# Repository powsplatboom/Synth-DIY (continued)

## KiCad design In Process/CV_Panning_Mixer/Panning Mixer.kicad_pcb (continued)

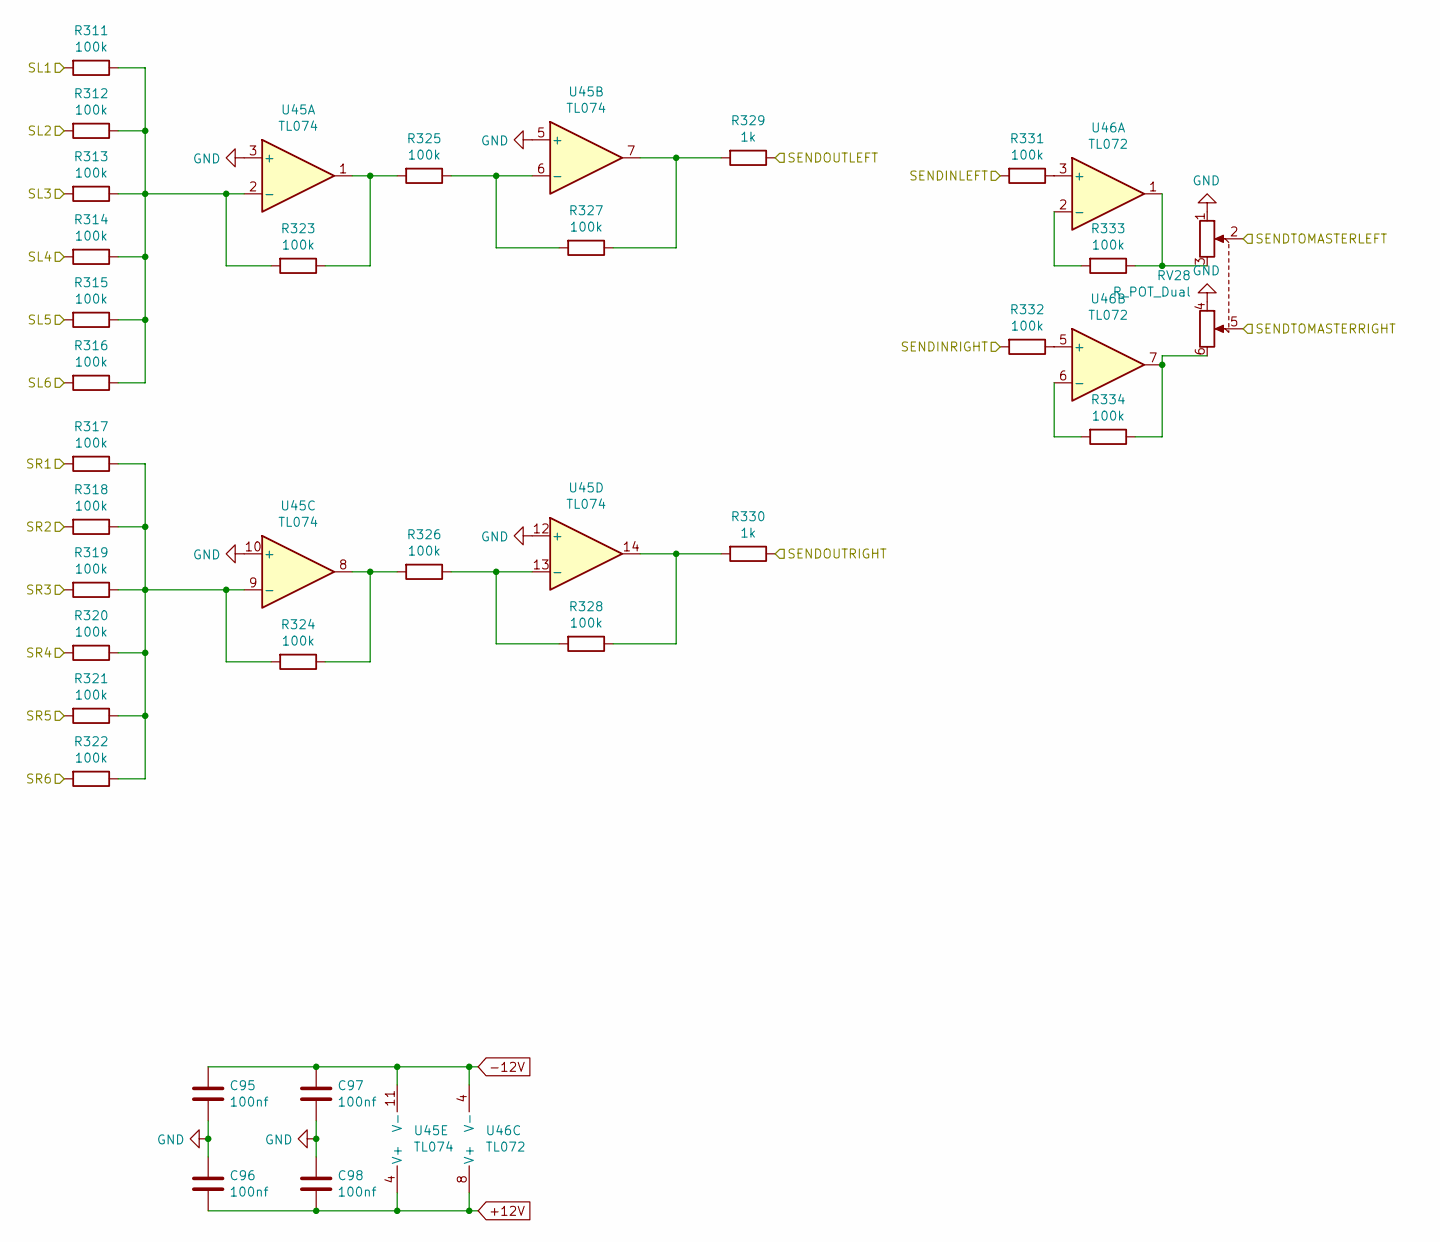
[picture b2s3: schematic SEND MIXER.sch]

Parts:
C91, C92, C93, C94: 100nf; C_0603_1608Metric
R287, R288, R289, R290, R291, R292, R293, R294, R295, R296, R297, R298, R299, R300, R301, R302, R303, R304, R307, R308, R309, R310: 100k; R_0603_1608Metric
R305, R306: 1k; R_0603_1608Metric
RV27: R_POT_Dual; Potentiometer_Alpha_RD902F-40-00D_Dual_Vertical
U43: TL074; SOIC-14_3.9x8.7mm_P1.27mm
U44: TL072; SOIC-8_3.9x4.9mm_P1.27mm

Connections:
+12V: C92.2, C94.2, U43.4 (V+), U44.8 (V+); also elsewhere on the board
-12V: C91.1, C93.1, U43.11 (V-), U44.4 (V-); also elsewhere on the board
GND: C91.2, C92.1, C93.2, C94.1, RV27.1, RV27.4, U43.3 (+), U43.5 (+), U43.10 (+), U43.12 (+); also elsewhere on the board
unnamed: R287.1, R288.1, R289.1, R290.1, R291.1, R292.1, R299.2, U43.2 (-)
unnamed: R293.1, R294.1, R295.1, R296.1, R297.1, R298.1, R300.2, U43.9 (-)
unnamed: R299.1, R301.2, U43.1
unnamed: R300.1, R302.2, U43.8
unnamed: R301.1, R303.2, U43.6 (-)
unnamed: R302.1, R304.2, U43.13 (-)
unnamed: R303.1, R305.2, U43.7
unnamed: R304.1, R306.2, U43.14
unnamed: R307.1, U44.3 (+)
unnamed: R308.1, U44.5 (+)
unnamed: R309.1, RV27.3, U44.1
unnamed: R309.2, U44.2 (-)
unnamed: R310.1, RV27.6, U44.7
unnamed: R310.2, U44.6 (-)
SENDINRIGHT_1: R308.2; also elsewhere on the board
SENDOUTLEFT_1: R305.1; also elsewhere on the board
SENDOUTRIGHT_1: R306.1; also elsewhere on the board
SENDTOMASTERLEFT_1: RV27.2; also elsewhere on the board
SENDTOMASTERRIGHT_1: RV27.5; also elsewhere on the board
SL1_1: R287.2; also elsewhere on the board
SL2_1: R288.2; also elsewhere on the board
SL3_1: R289.2; also elsewhere on the board
SL4_1: R290.2; also elsewhere on the board
SL5_1: R291.2; also elsewhere on the board
SL6_1: R292.2; also elsewhere on the board
SR1_1: R293.2; also elsewhere on the board
SR2_1: R294.2; also elsewhere on the board
SR3_1: R295.2; also elsewhere on the board
SR4_1: R296.2; also elsewhere on the board
SR5_1: R297.2; also elsewhere on the board
SR6_1: R298.2; also elsewhere on the board

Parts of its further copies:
C95, C96, C97, C98: 100nf; C_0603_1608Metric
R311, R312, R313, R314, R315, R316, R317, R318, R319, R320, R321, R322, R323, R324, R325, R326, R327, R328, R331, R332, R333, R334: 100k; R_0603_1608Metric
R329, R330: 1k; R_0603_1608Metric
RV28: R_POT_Dual; Potentiometer_Alpha_RD902F-40-00D_Dual_Vertical
U45: TL074; SOIC-14_3.9x8.7mm_P1.27mm
U46: TL072; SOIC-8_3.9x4.9mm_P1.27mm

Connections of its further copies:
+12V: C96.2, C98.2, U45.4 (V+), U46.8 (V+); also elsewhere on the board
-12V: C95.1, C97.1, U45.11 (V-), U46.4 (V-); also elsewhere on the board
GND: C95.2, C96.1, C97.2, C98.1, RV28.1, RV28.4, U45.3 (+), U45.5 (+), U45.10 (+), U45.12 (+); also elsewhere on the board
unnamed: R311.1, R312.1, R313.1, R314.1, R315.1, R316.1, R323.2, U45.2 (-)
unnamed: R317.1, R318.1, R319.1, R320.1, R321.1, R322.1, R324.2, U45.9 (-)
unnamed: R323.1, R325.2, U45.1
unnamed: R324.1, R326.2, U45.8
unnamed: R325.1, R327.2, U45.6 (-)
unnamed: R326.1, R328.2, U45.13 (-)
unnamed: R327.1, R329.2, U45.7
unnamed: R328.1, R330.2, U45.14
unnamed: R331.1, U46.3 (+)
unnamed: R332.1, U46.5 (+)
unnamed: R333.1, RV28.3, U46.1
unnamed: R333.2, U46.2 (-)
unnamed: R334.1, RV28.6, U46.7
unnamed: R334.2, U46.6 (-)
SENDINRIGHT_2: R332.2; also elsewhere on the board
SENDOUTLEFT_2: R329.1; also elsewhere on the board
SENDOUTRIGHT_2: R330.1; also elsewhere on the board
SENDTOMASTERLEFT_2: RV28.2; also elsewhere on the board
SENDTOMASTERRIGHT_2: RV28.5; also elsewhere on the board
SL1_2: R311.2; also elsewhere on the board
SL2_2: R312.2; also elsewhere on the board
SL3_2: R313.2; also elsewhere on the board
SL4_2: R314.2; also elsewhere on the board
SL5_2: R315.2; also elsewhere on the board
SL6_2: R316.2; also elsewhere on the board
SR1_2: R317.2; also elsewhere on the board
SR2_2: R318.2; also elsewhere on the board
SR3_2: R319.2; also elsewhere on the board
SR4_2: R320.2; also elsewhere on the board
SR5_2: R321.2; also elsewhere on the board
SR6_2: R322.2; also elsewhere on the board

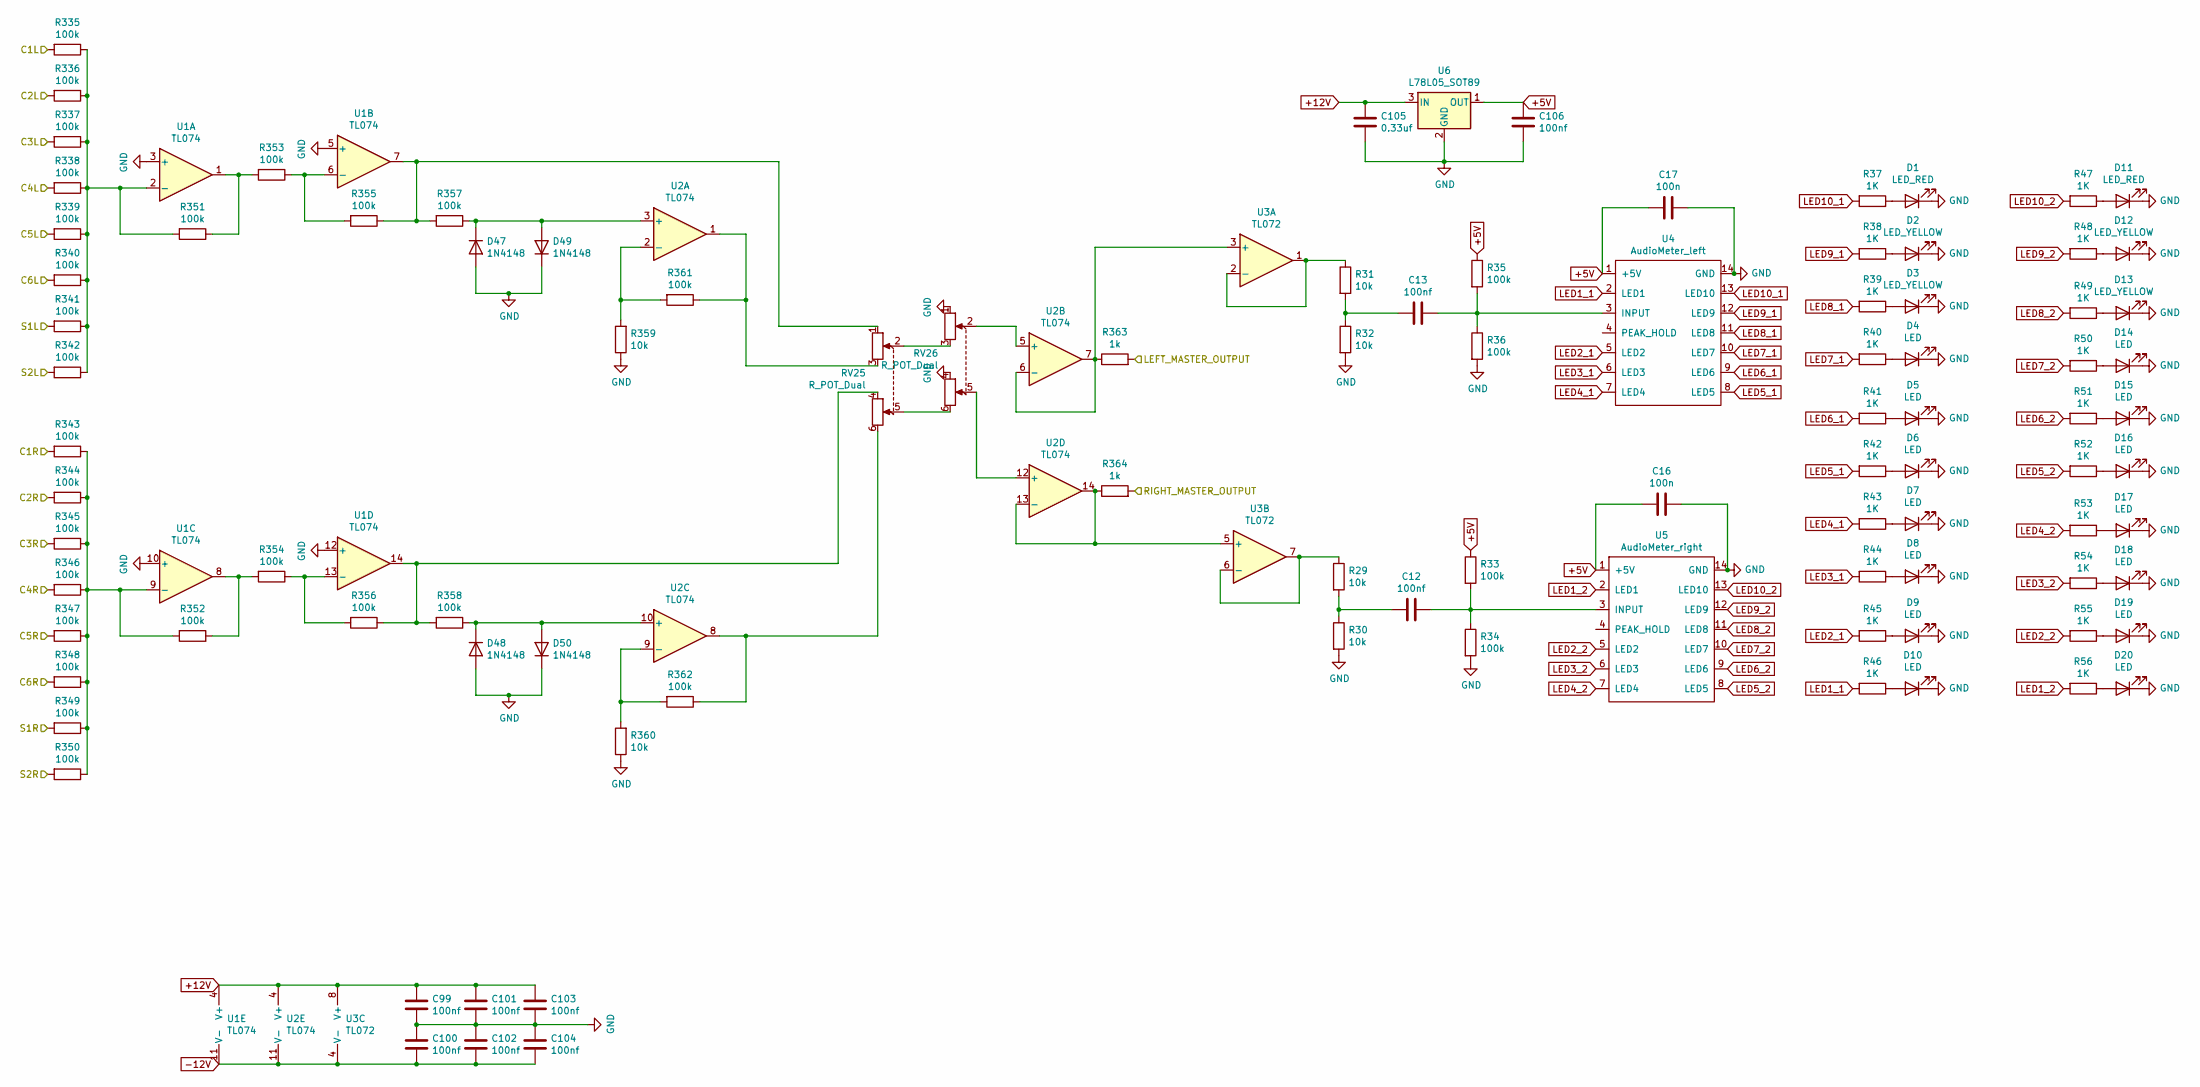
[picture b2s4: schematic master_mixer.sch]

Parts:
C12, C13, C99, C100, C101, C102, C103, C104, C106: 100nf; C_0603_1608Metric
C16, C17: 100n; C_0603_1608Metric
C105: 0.33uf; C_0603_1608Metric
D1, D11: LED_RED; LED_0805_2012Metric
D2, D3, D12, D13: LED_YELLOW; LED_0805_2012Metric
D4, D5, D6, D7, D8, D9, D10, D14, D15, D16, D17, D18, D19, D20: LED; LED_0805_2012Metric
D47, D48, D49, D50: 1N4148; D_DO-35_SOD27_P7.62mm_Horizontal
R29, R30, R31, R32, R359, R360: 10k; R_0603_1608Metric
R33, R34, R35, R36, R335, R336, R337, R338, R339, R340, R341, R342, R343, R344, R345, R346, R347, R348, R349, R350, R351, R352, R353, R354, R355, R356, R357, R358, R361, R362: 100k; R_0603_1608Metric
R37, R38, R39, R40, R41, R42, R43, R44, R45, R46, R47, R48, R49, R50, R51, R52, R53, R54, R55, R56: 1K; R_0603_1608Metric
R363, R364: 1k; R_0603_1608Metric
RV25, RV26: R_POT_Dual; Potentiometer_Alpha_RD902F-40-00D_Dual_Vertical
U1, U2: TL074; SOIC-14_3.9x8.7mm_P1.27mm
U3: TL072; SOIC-8_3.9x4.9mm_P1.27mm
U4: AudioMeter_left; DIP-14_W7.62mm_Socket_LongPads
U5: AudioMeter_right; DIP-14_W7.62mm_Socket_LongPads
U6: L78L05_SOT89; SOT-89-3

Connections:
+5V: C16.1, C17.1, C106.1, R33.1, R35.1, U4.1 (+5V), U5.1 (+5V), U6.1 (OUT)
+12V: C99.1, C101.1, C103.1, C105.1, U1.4 (V+), U2.4 (V+), U3.8 (V+), U6.3 (IN); also elsewhere on the board
-12V: C100.2, C102.2, C104.2, U1.11 (V-), U2.11 (V-), U3.4 (V-); also elsewhere on the board
GND: C16.2, C17.2, C99.2, C100.1, C101.2, C102.1, C103.2, C104.1, C105.2, C106.2, D1.1 (K), D2.1 (K), D3.1 (K), D4.1 (K), D5.1 (K), D6.1 (K), D7.1 (K), D8.1 (K), D9.1 (K), D10.1 (K), D11.1 (K), D12.1 (K), D13.1 (K), D14.1 (K), D15.1 (K), D16.1 (K), D17.1 (K), D18.1 (K), D19.1 (K), D20.1 (K), D47.2 (A), D48.2 (A), D49.1 (K), D50.1 (K), R30.2, R32.2, R34.2, R36.2, R359.1, R360.1, RV26.1, RV26.4, U1.3 (+), U1.5 (+), U1.10 (+), U1.12 (+), U4.14 (GND), U5.14 (GND), U6.2 (GND); also elsewhere on the board
LED1_1: R46.2, U4.2 (LED1)
LED1_2: R56.2, U5.2 (LED1)
LED2_1: R45.2, U4.5 (LED2)
LED2_2: R55.2, U5.5 (LED2)
LED3_1: R44.2, U4.6 (LED3)
LED3_2: R54.2, U5.6 (LED3)
LED4_1: R43.2, U4.7 (LED4)
LED4_2: R53.2, U5.7 (LED4)
LED5_1: R42.2, U4.8 (LED5)
LED5_2: R52.2, U5.8 (LED5)
LED6_1: R41.2, U4.9 (LED6)
LED6_2: R51.2, U5.9 (LED6)
LED7_1: R40.2, U4.10 (LED7)
LED7_2: R50.2, U5.10 (LED7)
LED8_1: R39.2, U4.11 (LED8)
LED8_2: R49.2, U5.11 (LED8)
LED9_1: R38.2, U4.12 (LED9)
LED9_2: R48.2, U5.12 (LED9)
LED10_1: R37.2, U4.13 (LED10)
LED10_2: R47.2, U5.13 (LED10)
LEFT_MASTER_OUTPUT: R363.2; also elsewhere on the board
unnamed: C12.1, R33.2, R34.1, U5.3 (INPUT)
unnamed: C12.2, R29.2, R30.1
unnamed: C13.1, R35.2, R36.1, U4.3 (INPUT)
unnamed: C13.2, R31.2, R32.1
unnamed: D1.2 (A), R37.1
unnamed: D2.2 (A), R38.1
unnamed: D3.2 (A), R39.1
unnamed: D4.2 (A), R40.1
unnamed: D5.2 (A), R41.1
unnamed: D6.2 (A), R42.1
unnamed: D7.2 (A), R43.1
unnamed: D8.2 (A), R44.1
unnamed: D9.2 (A), R45.1
unnamed: D10.2 (A), R46.1
unnamed: D11.2 (A), R47.1
unnamed: D12.2 (A), R48.1
unnamed: D13.2 (A), R49.1
unnamed: D14.2 (A), R50.1
unnamed: D15.2 (A), R51.1
unnamed: D16.2 (A), R52.1
unnamed: D17.2 (A), R53.1
unnamed: D18.2 (A), R54.1
unnamed: D19.2 (A), R55.1
unnamed: D20.2 (A), R56.1
unnamed: D47.1 (K), D49.2 (A), R357.1, U2.3 (+)
unnamed: D48.1 (K), D50.2 (A), R358.1, U2.10 (+)
unnamed: R29.1, U3.6 (-), U3.7
unnamed: R31.1, U3.1, U3.2 (-)
unnamed: R335.1, R336.1, R337.1, R338.1, R339.1, R340.1, R341.1, R342.1, R351.2, U1.2 (-)
unnamed: R343.1, R344.1, R345.1, R346.1, R347.1, R348.1, R349.1, R350.1, R352.2, U1.9 (-)
unnamed: R351.1, R353.2, U1.1
unnamed: R352.1, R354.2, U1.8
unnamed: R353.1, R355.2, U1.6 (-)
unnamed: R354.1, R356.2, U1.13 (-)
unnamed: R355.1, R357.2, RV25.1, U1.7
unnamed: R356.1, R358.2, RV25.4, U1.14
unnamed: R359.2, R361.2, U2.2 (-)
unnamed: R360.2, R362.2, U2.9 (-)
unnamed: R361.1, RV25.3, U2.1
unnamed: R362.1, RV25.6, U2.8
unnamed: R363.1, U2.6 (-), U2.7, U3.3 (+)
unnamed: R364.1, U2.13 (-), U2.14, U3.5 (+)
unnamed: RV25.2, RV26.3
unnamed: RV25.5, RV26.6
unnamed: RV26.2, U2.5 (+)
unnamed: RV26.5, U2.12 (+)
OUT_LEFT1: R335.2; also elsewhere on the board
OUT_LEFT2: R336.2; also elsewhere on the board
OUT_LEFT3: R337.2; also elsewhere on the board
OUT_LEFT4: R338.2; also elsewhere on the board
OUT_LEFT5: R339.2; also elsewhere on the board
OUT_LEFT6: R340.2; also elsewhere on the board
OUT_RIGHT1: R343.2; also elsewhere on the board
OUT_RIGHT2: R344.2; also elsewhere on the board
OUT_RIGHT3: R345.2; also elsewhere on the board
OUT_RIGHT4: R346.2; also elsewhere on the board
OUT_RIGHT5: R347.2; also elsewhere on the board
OUT_RIGHT6: R348.2; also elsewhere on the board
RIGHT_MASTER_OUTPUT: R364.2; also elsewhere on the board
SENDTOMASTERLEFT_1: R341.2; also elsewhere on the board
SENDTOMASTERLEFT_2: R342.2; also elsewhere on the board
SENDTOMASTERRIGHT_1: R349.2; also elsewhere on the board
SENDTOMASTERRIGHT_2: R350.2; also elsewhere on the board

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
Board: 4 copper layers, 633 parts (122 on the bottom side), 482 nets, no tracks yet.

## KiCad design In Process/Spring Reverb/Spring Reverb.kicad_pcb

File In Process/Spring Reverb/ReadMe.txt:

Board has been spun, but not populated. Will respin before testing, as some component circuit blocks have been discovered to have issues.

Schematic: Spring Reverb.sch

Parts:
C1, C2, C6, C10, C28, C39, C41, C42, C53: 10u; CP_Elec_4x5.3
C3, C7, C8, C9, C11, C12, C13, C14, C15, C16, C17, C18, C19, C20, C21, C22, C23, C24, C26, C27, C29, C30, C33, C34, C35, C36, C44, C45, C64: 100n; C_0603_1608Metric
C4: 0.33u; C_0603_1608Metric
C5, C65, C66, C67: 10uf; CP_Elec_4x5.3
C25: 22n; C_0603_1608Metric
C31, C38, C50, C51, C58, C59: 1nf; C_0603_1608Metric
C32: 470p; C_0603_1608Metric
C37, C55, C56: 4.7nf; C_0603_1608Metric
C40, C60, C61: 0.47nf; C_0603_1608Metric
C43: 100p; C_0603_1608Metric
C46: 22u; CP_Elec_4x5.3
C49, C62: 22p; C_0603_1608Metric
C63: 100nf; C_0603_1608Metric
D1, D2: B5819W; D_SOD-123
D3, D4, D11, D13: 1N4148; D_SOD-123
D5, D6, D7, D8, D9, D10, D12, D16, D17, D18, D19, D20, D21, D22, D23, D24, D25: LED; LED_1206_3216Metric_Pad1.42x1.75mm_HandSolder
D14: LED_RED; LED_1206_3216Metric_Pad1.42x1.75mm_HandSolder
D15: LED_YELLOW; LED_1206_3216Metric_Pad1.42x1.75mm_HandSolder
IC1: THAT4305Q16-U; QSOP-16_3.9x4.9mm_P0.635mm; Manufacturer_Part_Number THAT4305Q16-U
J1: Conn_02x05_Odd_Even; PinHeader_2x05_P2.54mm_Vertical
J2, J3, J4, J5, J6, J7, J8, J9, J10, J11, J13, J14, J18, J19: PJ301_THONKICONN; PJ-3001_Mono_Phone
Q1: BC849; SOT-23
Q2: BC859; SOT-23
Q3, Q4, Q11, Q12, Q13, Q14, Q15: BC848; SOT-23
Q5, Q6, Q7, Q8, Q9, Q10: BC858; SOT-23
R1, R2, R3, R7, R8, R9, R10, R13, R15, R24, R32, R36, R37, R60, R61, R62, R63, R91, R98, R99, R100, R101, R102, R103, R121, R122, R127, R128, R129, R130, R132, R133, R144, R145, R146, R147, R148, R149, R150, R151, R152: 100k; R_0603_1608Metric
R4, R19, R20, R34, R39, R43, R45, R46, R48, R50, R52, R56, R57, R66, R67, R73, R74, R75, R76, R77, R78, R81, R82, R87, R88, R93, R94, R108, R109, R115, R116, R119, R120, R124, R125, R126: 10k; R_0603_1608Metric
R5: 50k; R_0603_1608Metric
R6: 150; R_0603_1608Metric
R11, R12: 6k8; R_0603_1608Metric
R14, R18, R92: 5k; R_0603_1608Metric
R16, R17: 10; R_0603_1608Metric
R21: 3k3; R_0603_1608Metric
R22, R23, R95: 1k; R_0603_1608Metric
R25, R53, R70, R96, R97, R110, R111, R112, R113: 20k; R_0603_1608Metric
R26: 40k; R_0603_1608Metric
R31: 2k2; R_0603_1608Metric
R33: 220; R_0603_1608Metric
R35, R38, R47, R51, R58, R59, R64, R65, R79, R80, R85, R86: 220R; R_0603_1608Metric
R40, R68, R69: 1.8k; R_0603_1608Metric
R41, R71, R72: 470k; R_0603_1608Metric
R42: 22k; R_0603_1608Metric
R44: 2k; R_0603_1608Metric
R49, R83, R84: 4.7k; R_0603_1608Metric
R54: 33k; R_0603_1608Metric
R55: 6k2; R_0603_1608Metric
R89, R131: 5k1; R_0603_1608Metric
R90: 360k; R_0603_1608Metric
R104, R105: 82k; R_0603_1608Metric
R106, R107, R117, R118: 100R; R_0603_1608Metric
R114: 1k43; R_0603_1608Metric
R123: 487k; R_0603_1608Metric
R134, R135, R136, R137, R138, R139, R140, R141, R142, R143: 1K; R_0603_1608Metric
RV3, RV4, RV5, RV6, RV7, RV8, RV9, RV10, RV11, RV13, RV14: 100k; Potentiometer_Alpha_RD901F-40-00D_Single_Vertical
RV12, RV15, RV16, RV19, RV20: 10k; Potentiometer_Alpha_RD901F-40-00D_Single_Vertical
RV17, RV18: 100k; Potentiometer_Bourns_3266Y_Vertical
RV21, RV22: R_POT_Dual_Separate; Potentiometer_Alpha_RD902F-40-00D_Dual_Vertical
SW1, SW2, SW3, SW4, SW5: SW_DPDT_x2; DPDT_ThroughHole
TP5, TP6: TestPoint A; TestPoint_Bridge_Pitch2.54mm_Drill1.0mm
TP7, TP8: TestPoint C; TestPoint_Bridge_Pitch2.54mm_Drill1.0mm
TP9, TP12: TestPoint D; TestPoint_Bridge_Pitch2.54mm_Drill1.0mm
TP10, TP11: TestPoint B; TestPoint_Bridge_Pitch2.54mm_Drill1.0mm
U1, U3, U4, U6, U7, U9, U11, U12: TL074; SOIC-14_3.9x8.7mm_P1.27mm
U2, U8, U10: LM13700; SO-16_3.9x9.9mm_P1.27mm
U5: NE5532; SOIC-8_3.9x4.9mm_P1.27mm
U13: L78L05_SO8; SOIC-8_3.9x4.9mm_P1.27mm
U15: AudioMeter_left; DIP-14_W7.62mm_Socket_LongPads

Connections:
+5V: C7.1, C64.1, R127.1, U13.1 (OUT), U15.1 (+5V)
+12V: C1.1, C4.1, C8.2, C11.2, C13.2, C15.2, C17.2, C19.2, C21.2, C23.2, C26.2, C29.2, C33.2, C35.2, C44.1, C46.1, D1.1 (K), IC1.9 (VCC), Q1.3 (C), R11.2, R22.2, R23.2, R95.2, R96.2, R97.2, R110.2, R111.2, R112.2, R113.2, RV4.3, RV7.3, RV8.3, RV12.1, RV16.1, RV17.1, RV18.1, U1.4 (V+), U2.11 (V+), U3.4 (V+), U4.4 (V+), U5.8 (V+), U6.4 (V+), U7.4 (V+), U8.11 (V+), U9.4 (V+), U10.11 (V+), U11.4 (V+), U12.4 (V+), U13.8 (IN)
-12V: C2.2, C9.2, C12.2, C14.2, C16.2, C18.2, C20.2, C22.2, C24.2, C27.2, C30.2, C34.2, C36.2, C45.1, D2.2 (A), IC1.8 (VEE), Q2.2 (E), Q3.2 (E), Q4.2 (E), Q11.2 (E), R12.1, R41.1, R71.1, R72.1, RV4.1, RV7.1, RV8.1, RV12.3, RV16.3, RV17.3, RV18.3, U1.11 (V-), U2.6 (V-), U3.11 (V-), U4.11 (V-), U5.4 (V-), U6.11 (V-), U7.11 (V-), U8.6 (V-), U9.11 (V-), U10.6 (V-), U11.11 (V-), U12.11 (V-)
Comp_Out: C3.2, C49.2, R70.1, U1.12 (+), U4.1
Cutoff_CV: J5.3, RV3.3
Cutoff_CV_Left: J8.3, RV6.3, SW2.2 (B)
Cutoff_CV_Right: J9.3, RV9.3
FeedBack: C65.2, R3.2
Filter_Output: C40.2, C41.2, C42.2, RV5.3
Filter_Output_Left: C60.2, R102.2, RV10.3
Filter_Output_Right: C61.2, R103.2, RV11.3
GND: C1.2, C2.1, C4.2, C7.2, C8.1, C9.1, C11.1, C12.1, C13.1, C14.1, C15.1, C16.1, C17.1, C18.1, C19.1, C20.1, C21.1, C22.1, C23.1, C24.1, C25.1, C26.1, C27.1, C29.1, C30.1, C33.1, C34.1, C35.1, C36.1, C43.1, C44.2, C45.2, C46.2, C53.2, C64.2, D14.1 (K), D15.1 (K), D16.1 (K), D17.1 (K), D18.1 (K), D19.1 (K), D20.1 (K), D21.1 (K), D22.1 (K), D23.1 (K), IC1.11 (EC+), J1.3, J1.4, J1.5, J1.6, J1.7, J1.8, J2.1, J3.1, J4.1, J4.2, J5.1, J6.1, J7.1, J8.1, J9.1, J11.1, J13.1, J14.1, J18.1, J19.1, Q6.1 (B), Q9.1 (B), Q10.1 (B), R4.1, R6.1, R14.1, R18.1, R32.1, R33.1, R35.2, R38.2, R40.2, R47.2, R51.2, R58.2, R59.2, R64.2, R65.2, R68.2, R69.2, R79.2, R80.2, R85.2, R86.2, R92.1, R106.2, R107.2, R116.2, R117.2, R118.2, R128.2, R129.2, R130.2, RV3.1, RV5.1, RV6.1, RV9.1, RV10.1, RV11.1, RV13.1, RV14.1, RV15.1, RV19.1, RV20.1, RV21.1, RV21.4, RV22.1, RV22.4, SW3.5 (B), SW4.5 (B), SW5.2 (B), U1.3 (+), U1.5 (+), U1.10 (+), U3.5 (+), U4.3 (+), U4.5 (+), U4.10 (+), U6.3 (+), U6.10 (+), U6.12 (+), U7.5 (+), U9.5 (+), U11.3 (+), U11.10 (+), U12.5 (+), U12.10 (+), U13.2 (GND), U13.3 (GND), U13.6 (GND), U13.7 (GND), U15.14 (GND)
Inverted_Cutoff_CV_Left: J9.2
Inverted_Left_VCA: J7.2, SW1.5 (B)
LED1_1: R143.2, U15.2 (LED1)
LED2_1: R142.2, U15.5 (LED2)
LED3_1: R141.2, U15.6 (LED3)
LED4_1: R140.2, U15.7 (LED4)
LED5_1: R139.2, U15.8 (LED5)
LED6_1: R138.2, U15.9 (LED6)
LED7_1: R137.2, U15.10 (LED7)
LED8_1: R136.2, U15.11 (LED8)
LED9_1: R135.2, U15.12 (LED9)
LED10_1: R134.2, U15.13 (LED10)
LED_drive: R114.1, R124.2, RV15.2, U4.12 (+)
LeftVCA_output: J13.3, R132.1, RV19.3, RV22.3, U11.7
Left_Out: C66.2, J18.3
Left_VCA: J6.3, R98.2, SW1.2 (B)
Left_in: J2.3, J3.2, R1.2, RV21.3
unnamed: C3.1, R4.2, U5.3 (+)
unnamed: C5.1, R5.1, U1.1
unnamed: C6.1, R6.2
unnamed: C6.2, J10.1, R21.1, U5.2 (-)
unnamed: C10.1, D3.2 (A), Q1.1 (B), R11.1
unnamed: C10.2, D4.1 (K), Q2.1 (B), R12.2
unnamed: C25.2, R31.1
unnamed: C28.1, R33.2
unnamed: C28.2, C32.1, R42.1, U5.6 (-)
unnamed: C31.1, U2.12, U3.10 (+)
unnamed: C31.2, D5.1 (K), D6.2 (A), R45.2, U3.1
unnamed: C32.2, R42.2, R44.1, U5.7
unnamed: C37.1, R49.1, U3.7
unnamed: C37.2, Q5.3 (C), R41.2, U3.6 (-)
unnamed: C38.1, U2.5, U3.12 (+)
unnamed: C38.2, SW3.3 (C), SW3.4 (A)
unnamed: C39.2, U6.6 (-), U6.7
unnamed: C40.1, R52.1, U3.13 (-), U3.14
unnamed: C41.1, R53.2
unnamed: C42.1, R54.2
unnamed: C43.2, R55.2
unnamed: C49.1, IC1.13 (VCA_OUT), R70.2, U4.2 (-)
unnamed: C50.1, U7.10 (+), U8.12
unnamed: C50.2, D7.1 (K), D8.2 (A), R75.2, U7.1
unnamed: C51.1, U9.10 (+), U10.12
unnamed: C51.2, D9.2 (A), D10.1 (K), R76.2, U9.1
unnamed: C53.1, IC1.4 (CT)
unnamed: C55.1, R83.1, U7.7
unnamed: C55.2, Q7.3 (C), R71.2, U7.6 (-)
unnamed: C56.1, R84.1, U9.7
unnamed: C56.2, Q8.3 (C), R72.2, U9.6 (-)
unnamed: C58.1, U7.12 (+), U8.5
unnamed: C58.2, SW4.3 (C), SW4.4 (A)
unnamed: C59.1, U9.12 (+), U10.5
unnamed: C59.2, SW5.1 (A), SW5.6 (C)
unnamed: C60.1, R87.1, U7.13 (-), U7.14
unnamed: C61.1, R88.1, U9.13 (-), U9.14
unnamed: C62.1, D11.1 (K), R89.1, R90.1, R94.2, U4.6 (-)
unnamed: C62.2, D11.2 (A), D13.1 (K), U4.7
unnamed: C63.1, R127.2, R128.1, U15.3 (INPUT)
unnamed: C63.2, R115.2, R116.1
unnamed: C65.1, R150.1, U1.7
unnamed: C66.1, R151.1, U12.7
unnamed: C67.1, R152.1, U12.8
unnamed: D1.2 (A), J1.9, J1.10
unnamed: D2.1 (K), J1.1, J1.2
unnamed: D3.1 (K), D4.2 (A), U5.1
unnamed: D5.2 (A), D6.1 (K), R45.1, U3.2 (-)
unnamed: D7.2 (A), D8.1 (K), R75.1, U7.2 (-)
unnamed: D9.1 (K), D10.2 (A), R76.1, U9.2 (-)
unnamed: D12.1 (K), Q11.3 (C)
unnamed: D12.2 (A), R95.1
unnamed: D14.2 (A), R134.1
unnamed: D15.2 (A), R135.1
unnamed: D16.2 (A), R136.1
unnamed: D17.2 (A), R137.1
unnamed: D18.2 (A), R138.1
unnamed: D19.2 (A), R139.1
unnamed: D20.2 (A), R140.1
unnamed: D21.2 (A), R141.1
unnamed: D22.2 (A), R142.1
unnamed: D23.2 (A), R143.1
unnamed: D24.1 (K), Q3.3 (C)
unnamed: D24.2 (A), R22.1
unnamed: D25.1 (K), Q4.3 (C)
unnamed: D25.2 (A), R23.1
unnamed: IC1.2 (RMS_IN), R54.1
unnamed: IC1.15 (VCA_IN), R53.1, R55.1
unnamed: J10.3, R16.1, R17.2, R21.2
unnamed: J11.3, R31.2, R32.2, U5.5 (+)
unnamed: Q1.2 (E), R16.2
unnamed: Q2.3 (C), R17.1
unnamed: Q3.1 (B), R19.2
unnamed: Q4.1 (B), R20.2
unnamed: Q5.1 (B), R36.1, R37.1, R40.1
unnamed: Q5.2 (E), Q6.2 (E), R49.2
unnamed: Q6.3 (C), R43.1, R48.2
unnamed: Q7.1 (B), R60.1, R61.1, R68.1
unnamed: Q7.2 (E), Q9.2 (E), R83.2
unnamed: Q8.1 (B), R62.1, R63.1, R69.1
unnamed: Q9.3 (C), R73.1, R81.2
unnamed: Q8.2 (E), Q10.2 (E), R84.2
unnamed: Q10.3 (C), R74.1, R82.2
unnamed: Q11.1 (B), R93.2
unnamed: Q12.1 (B), R102.1, R106.1, TP5.1
unnamed: Q12.2 (E), Q14.2 (E), R108.1, TP10.1
unnamed: Q12.3 (C), R110.1, R119.2, TP7.1
unnamed: Q13.1 (B), R103.1, R107.1, TP6.1
unnamed: Q13.2 (E), Q15.2 (E), R109.1, TP11.1
unnamed: Q13.3 (C), R111.1, R120.2, TP8.1
unnamed: Q14.1 (B), R117.1, R121.2
unnamed: Q14.3 (C), R112.1, R125.2, TP9.1
unnamed: Q15.1 (B), R118.1, R122.2
unnamed: Q15.3 (C), R113.1, R126.2, TP12.1
unnamed: R1.1, R2.1, R3.1, R5.2, U1.2 (-)
unnamed: R7.1, R9.2, U6.9 (-)
unnamed: R7.2, SW1.1 (A)
unnamed: R8.2, SW2.1 (A)
unnamed: R9.1, SW1.4 (A), U6.8
unnamed: R10.1, SW2.4 (A), U6.14
unnamed: R8.1, R10.2, U6.13 (-)
unnamed: R13.1, R14.2, U12.2 (-)
unnamed: R13.2, R19.1, U12.1
unnamed: R15.1, R18.2, U12.12 (+)
unnamed: R15.2, R20.1, U12.14
unnamed: R24.1, R25.2, U1.9 (-)
unnamed: R25.1, R26.2, U1.8
unnamed: R34.1, R35.1, R39.2, U2.13 (-)
unnamed: R34.2, SW3.1 (A)
unnamed: R36.2, RV3.2
unnamed: R37.2, RV4.2
unnamed: R38.1, U2.14 (+)
unnamed: R39.1, R46.2, U3.8, U3.9 (-)
unnamed: R43.2, U2.16
unnamed: R44.2, R50.1, U6.2 (-)
unnamed: R46.1, R51.1, U2.3 (+)
unnamed: R47.1, R52.2, U2.4 (-)
unnamed: R48.1, U2.1
unnamed: R50.2, U6.1, U6.5 (+)
unnamed: R56.1, R58.1, R66.2, U8.13 (-)
unnamed: R56.2, SW4.1 (A)
unnamed: R57.1, R59.1, R67.2, U10.13 (-)
unnamed: R57.2, SW5.4 (A)
unnamed: R60.2, RV6.2
unnamed: R61.2, RV7.2
unnamed: R62.2, RV8.2
unnamed: R63.2, RV9.2
unnamed: R64.1, U8.14 (+)
unnamed: R65.1, U10.14 (+)
unnamed: R66.1, R77.2, U7.8, U7.9 (-)
unnamed: R67.1, R78.2, U9.8, U9.9 (-)
unnamed: R73.2, U8.16
unnamed: R74.2, U10.16
unnamed: R77.1, R85.1, U8.3 (+)
unnamed: R78.1, R86.1, U10.3 (+)
unnamed: R79.1, R87.2, U8.4 (-)
unnamed: R80.1, R88.2, U10.4 (-)
unnamed: R81.1, U8.1
unnamed: R82.1, U10.1
unnamed: R90.2, RV12.2
unnamed: R91.1, R92.2, U4.13 (-)
unnamed: R91.2, R93.1, U4.14
unnamed: R96.1, RV13.3
unnamed: R97.1, RV14.3
unnamed: R99.2, RV13.2
unnamed: R100.1, R101.1, R105.2, U11.9 (-)
unnamed: R100.2, RV14.2
unnamed: R104.1, R108.2, U11.1, U12.3 (+)
unnamed: R98.1, R99.1, R104.2, U11.2 (-)
unnamed: R105.1, R109.2, U11.8, U12.13 (-)
unnamed: R115.1, U1.13 (-), U1.14
unnamed: R119.1, R132.2, U11.6 (-)
unnamed: R120.1, R133.2, U11.13 (-)
unnamed: R121.1, RV17.2
unnamed: R122.1, RV18.2
unnamed: R26.1, R123.1, R124.1, R131.2, U4.9 (-)
unnamed: R123.2, RV16.2
unnamed: R125.1, R129.1, U11.5 (+)
unnamed: R126.1, R130.1, U11.12 (+)
unnamed: R144.1, R145.1, R150.2, U1.6 (-)
unnamed: R144.2, RV19.2
unnamed: R145.2, RV20.2
unnamed: R146.1, R147.1, R151.2, U12.6 (-)
unnamed: R146.2, RV21.2
unnamed: R147.2, RV22.2
unnamed: R148.1, R149.1, R152.2, U12.9 (-)
unnamed: R148.2, RV21.5
unnamed: R149.2, RV22.5
unnamed: RV5.2, U3.3 (+)
unnamed: RV10.2, U7.3 (+)
unnamed: RV11.2, U9.3 (+)
unnamed: SW1.3 (C), SW1.6 (C)
unnamed: SW2.3 (C), SW2.6 (C)
Prefilter_Input: C5.2, SW3.2 (B)
RMS_out: IC1.5 (RMS_OUT), R89.2
RightVCA_output: J14.3, R133.1, RV20.3, RV22.6, U11.14
Right_Out: C67.2, J19.3
Right_VCA: J7.3, R101.2
Right_in: J3.3, R2.2, RV21.6
Spring_out: C39.1, SW4.2 (B), SW5.5 (B)
Threshold_out: D13.2 (A), R94.1, R114.2, RV15.3
VCA_Pre_CV: J4.3, R24.2
V_Comp: IC1.12 (EC-), R131.1, U4.8

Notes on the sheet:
Outputs
Inputs
Right Mixer
Left Mixer
Feedback Mixer
Everything after the transistors is 0.1% tolerance
Post-amplifier VCA
Post-Filter
2250R Coil Recovery Circuit
150R Coil Drive Circuit
Level Meter
Compressor
LED Driver
Power Supply Stuff
Compression Ratio and Makeup Gain
Inverting Threshold Amplifier
Must be NPO
Adjustable time constant, tau, with rotary switch: 3ms, 10ms, 25ms, 35ms, 75ms, 100ms approximately.
RMS Detector
VCA
Pre-Filter
Stereo Input Mixer Stage w/ feedback

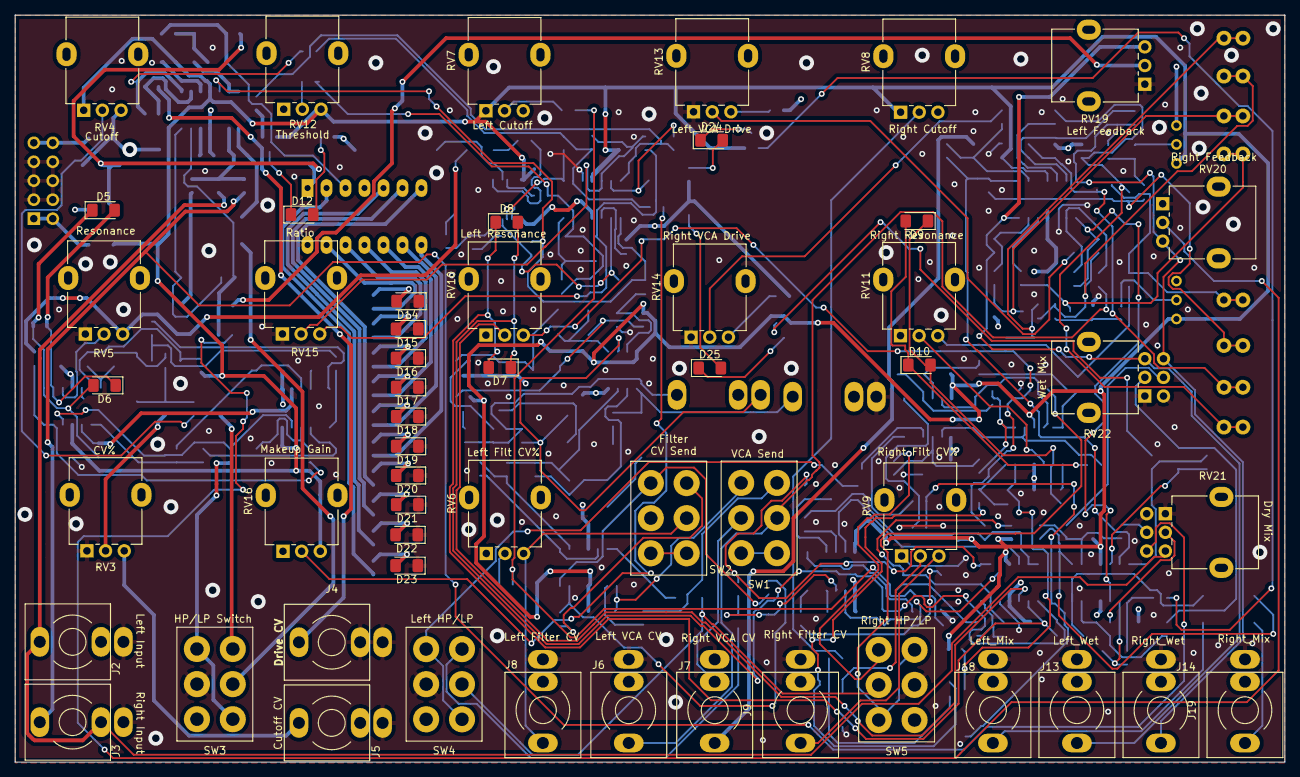
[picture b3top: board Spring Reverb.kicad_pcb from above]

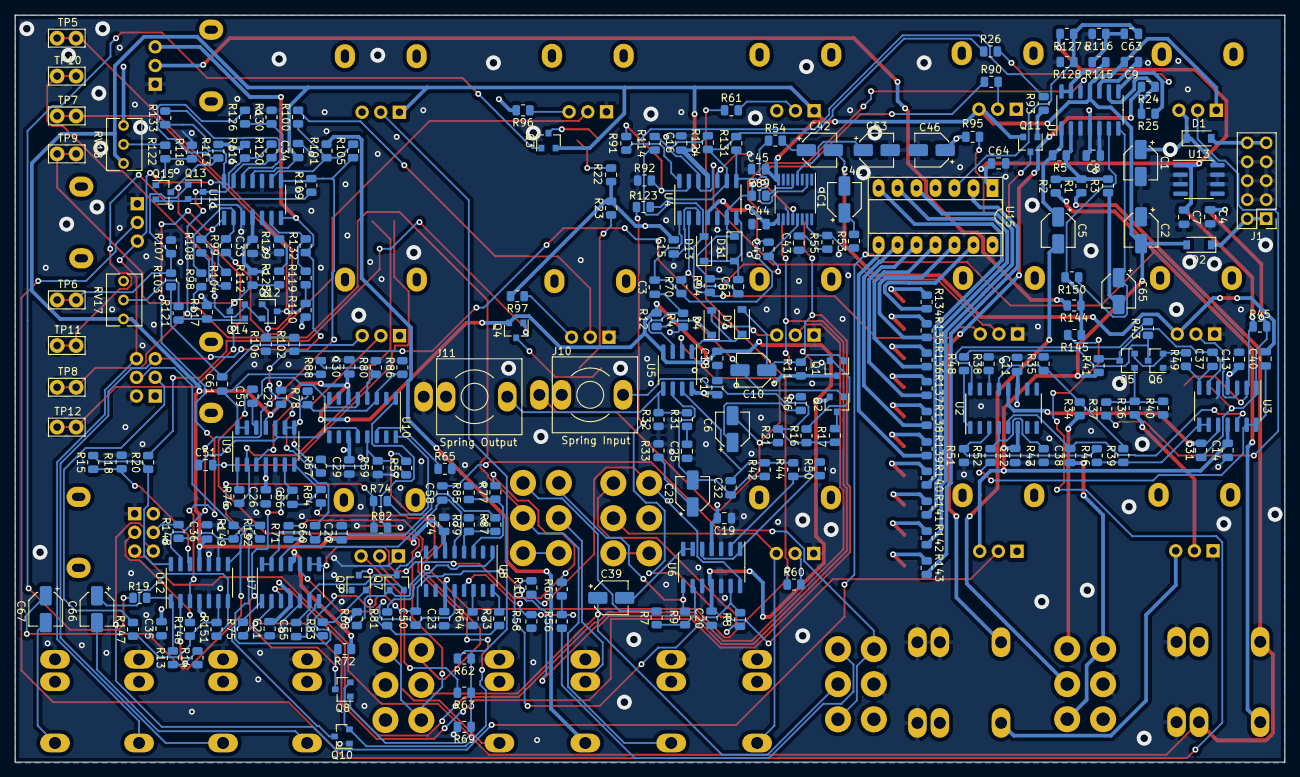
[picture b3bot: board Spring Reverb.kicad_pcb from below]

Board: 4 copper layers, 170.0 x 100.0 mm, 313 parts (259 on the bottom side), 211 nets.

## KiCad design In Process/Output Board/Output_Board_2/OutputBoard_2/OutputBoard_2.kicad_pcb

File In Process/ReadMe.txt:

This folder contains all of my files that are unifinished or have glaring issues that need fixed. Some have yet to be spun as boards, some have been spun and require updates and a respin, some are abandoned projects. These are work in progress, please don't order these PCBs.

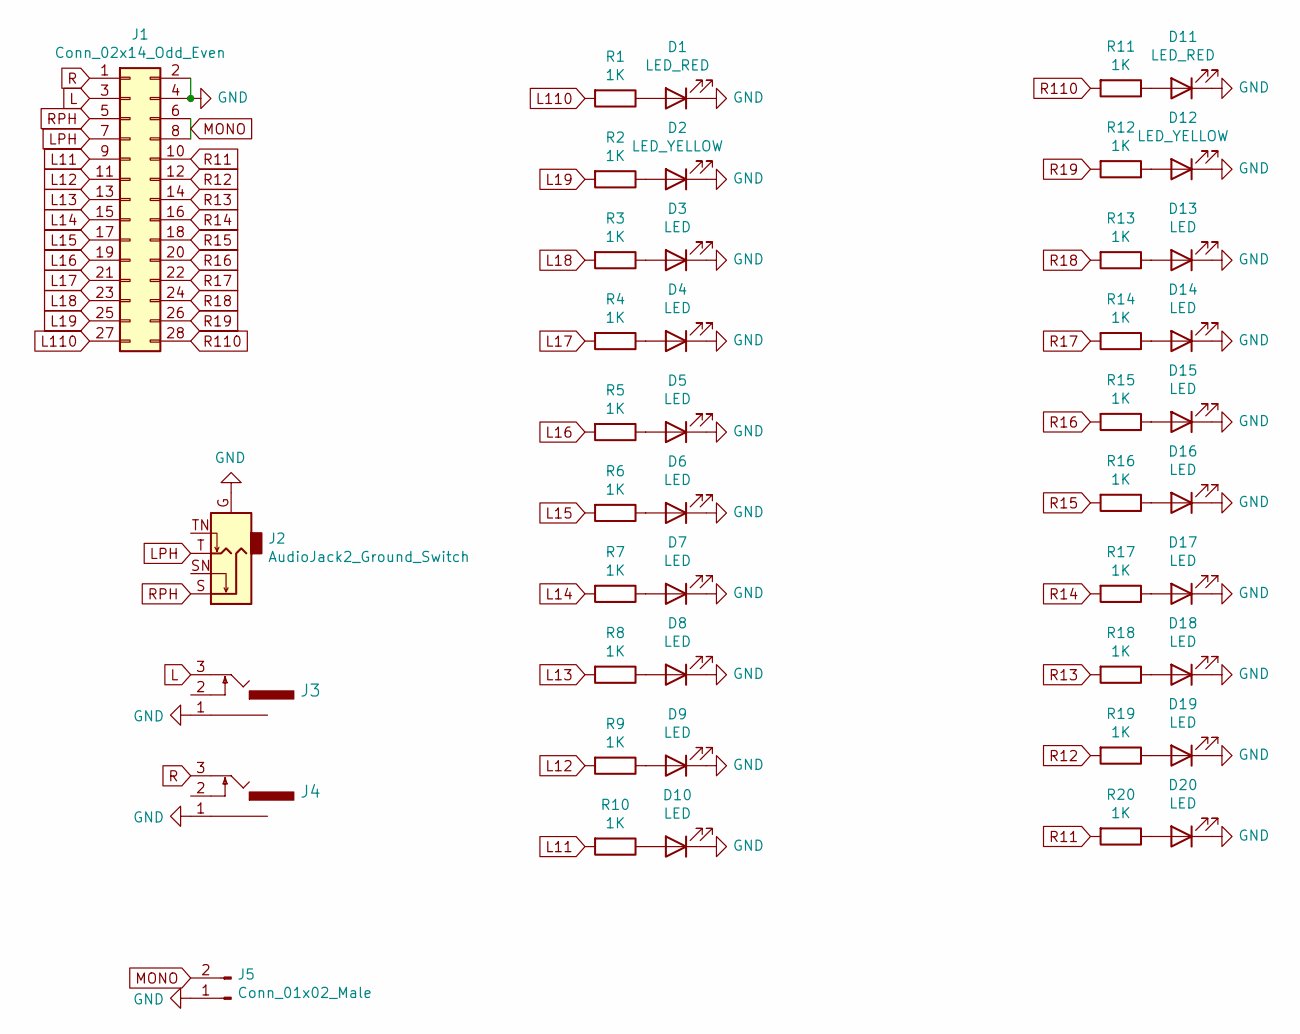
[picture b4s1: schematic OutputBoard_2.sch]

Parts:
D1, D11: LED_RED; LED_D5.0mm
D2, D12: LED_YELLOW; LED_D5.0mm
D3, D4, D5, D6, D7, D8, D9, D10, D13, D14, D15, D16, D17, D18, D19, D20: LED; LED_D5.0mm
J1: Conn_02x14_Odd_Even; PinSocket_2x14_P2.54mm_Vertical
J2: AudioJack2_Ground_Switch; Stereo_phon_jack_STX-3790
J3, J4: benjolin_1.6-eagle-import_PJ301_THONKICONN6; PJ-3001_Mono_Phone
J5: Conn_01x02_Male; JST_EH_B2B-EH-A_1x02_P2.50mm_Vertical
R1, R2, R3, R4, R5, R6, R7, R8, R9, R10, R11, R12, R13, R14, R15, R16, R17, R18, R19, R20: 1K; R_Axial_DIN0207_L6.3mm_D2.5mm_P7.62mm_Horizontal

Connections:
GND: D1.1 (K), D2.1 (K), D3.1 (K), D4.1 (K), D5.1 (K), D6.1 (K), D7.1 (K), D8.1 (K), D9.1 (K), D10.1 (K), D11.1 (K), D12.1 (K), D13.1 (K), D14.1 (K), D15.1 (K), D16.1 (K), D17.1 (K), D18.1 (K), D19.1 (K), D20.1 (K), J1.2, J1.4, J2.G, J3.1, J4.1, J5.1
L: J1.3, J3.3
L11: J1.9, R10.2
L12: J1.11, R9.2
L13: J1.13, R8.2
L14: J1.15, R7.2
L15: J1.17, R6.2
L16: J1.19, R5.2
L17: J1.21, R4.2
L18: J1.23, R3.2
L19: J1.25, R2.2
L110: J1.27, R1.2
LPH: J1.7, J2.T
MONO: J1.6, J1.8, J5.2
unnamed: D1.2 (A), R1.1
unnamed: D2.2 (A), R2.1
unnamed: D3.2 (A), R3.1
unnamed: D4.2 (A), R4.1
unnamed: D5.2 (A), R5.1
unnamed: D6.2 (A), R6.1
unnamed: D7.2 (A), R7.1
unnamed: D8.2 (A), R8.1
unnamed: D9.2 (A), R9.1
unnamed: D10.2 (A), R10.1
unnamed: D11.2 (A), R11.1
unnamed: D12.2 (A), R12.1
unnamed: D13.2 (A), R13.1
unnamed: D14.2 (A), R14.1
unnamed: D15.2 (A), R15.1
unnamed: D16.2 (A), R16.1
unnamed: D17.2 (A), R17.1
unnamed: D18.2 (A), R18.1
unnamed: D19.2 (A), R19.1
unnamed: D20.2 (A), R20.1
R: J1.1, J4.3
R11: J1.10, R20.2
R12: J1.12, R19.2
R13: J1.14, R18.2
R14: J1.16, R17.2
R15: J1.18, R16.2
R16: J1.20, R15.2
R17: J1.22, R14.2
R18: J1.24, R13.2
R19: J1.26, R12.2
R110: J1.28, R11.2
RPH: J1.5, J2.S
